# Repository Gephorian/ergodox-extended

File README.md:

# ErgoDox Extended

In a world where everyone is removing keys from their ErgoDox, I wanted more.

My goals for this keyboard were to take my existing design from 2018 and remove the Teensy,
while making it more compact, a little more stylish, and with several options for cases in
mind.

I used an ATMega32u4-au for the mcu because I wanted to be able to solder it by hand if I
needed. Same for the MCP23018-e/ss. I stuck with Mini-USB because, again, hand soldering.

There are options for SMD or through-hole diodes.

Cherry keyswitches, I've never used Gaterons or any others so I can't say whether they
would be compatible with the pcb.

This board works just like the original ErgoDox board; the same board can be used for
either half of the keyboard. Solder the logic components on the front, and diodes on the
front or back of the board. The silkscreen for diode direction is set up for `Row2Col` in
the firmware.

Everything should be included in the kicad project aside from the firmware. Make sure
to clone recursively so that it pulls the submodule(s).

Firmware is [here](https://github.com/Gephorian/qmk_firmware/tree/ergodox-extended) until
I get a PR merged into QMK.

## Manufacturing

I've used JLCPCB and Elecrow. Both are great. Go for 1.6mm, whatever color you want is
fine. I was able to generate a BOM using JLCPCB's plugin and get it partially assembled,
so that takes a lot of guesswork out of the soldering and debugging if you go that route.

## Contributing

Feel free to submit PRs and issues for fixes.

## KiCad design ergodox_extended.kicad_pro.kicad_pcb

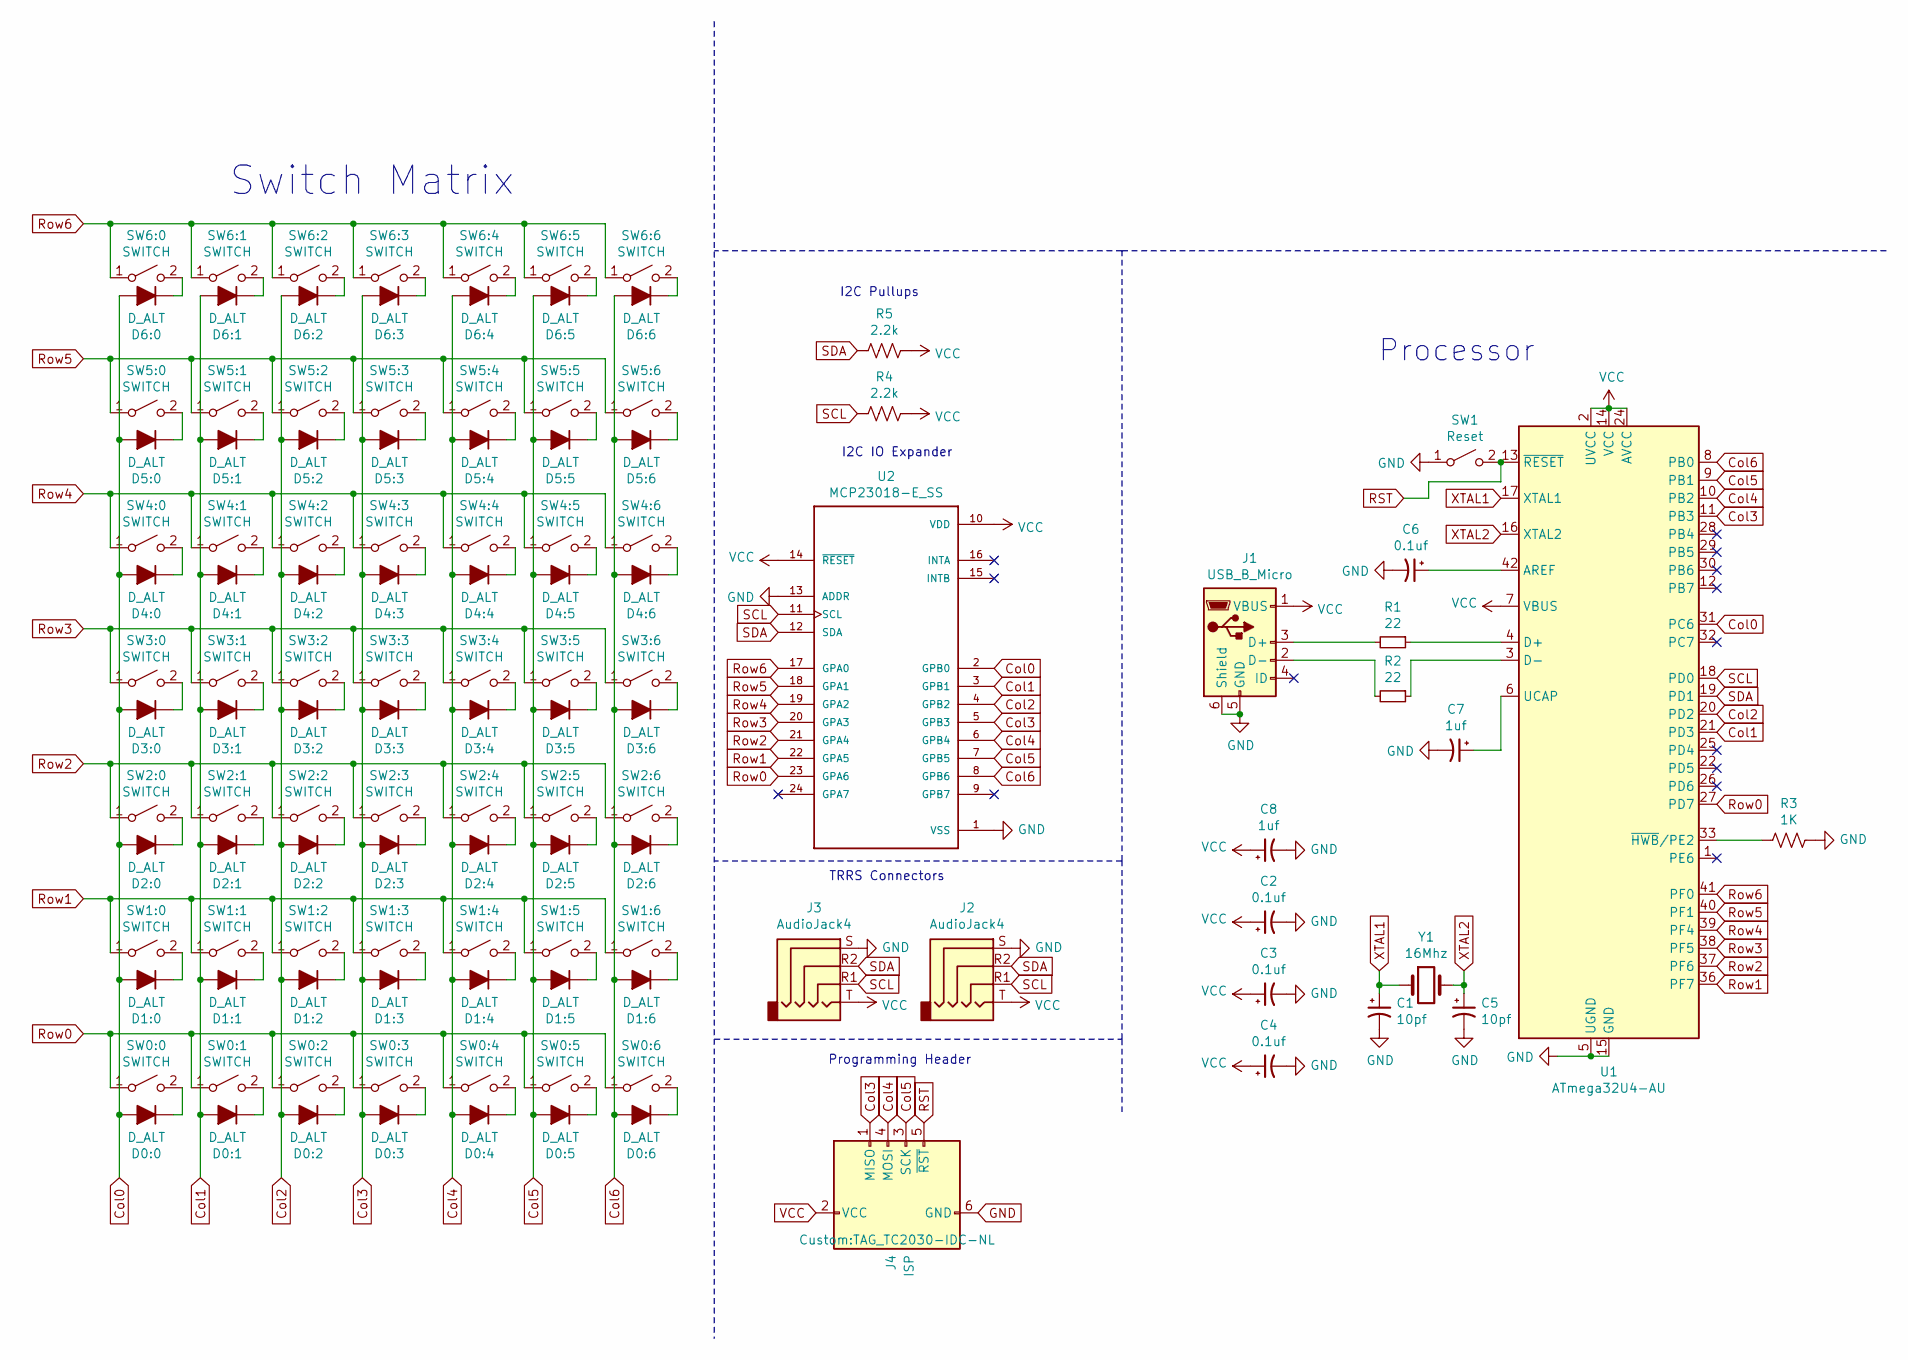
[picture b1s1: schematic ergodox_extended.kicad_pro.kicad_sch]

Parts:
C1, C5: 10pf; C_0402_1005Metric
C2, C3, C4, C6: 0.1uf; C_0603_1608Metric
C7, C8: 1uf; C_0805_2012Metric
D0:0, D0:1, D0:2, D0:3, D0:4, D0:5, D0:6, D1:0, D1:1, D1:2, D1:3, D1:4, D1:5, D1:6, D2:0, D2:1, D2:2, D2:3, D2:4, D2:5, D2:6, D3:0, D3:1, D3:2, D3:3, D3:4, D3:5, D3:6, D4:0, D4:1, D4:2, D4:3, D4:4, D4:5, D4:6, D5:0, D5:1, D5:2, D5:3, D5:4, D5:5, D5:6, D6:0, D6:1, D6:2, D6:3, D6:4, D6:5, D6:6: D_ALT; DIODE
J1: USB_B_Micro; USBMINImod
J2, J3: AudioJack4; SJ-43514-SMT
J4: ISP; TAG_TC2030-IDC-NL
R1, R2: 22; R_0805_2012Metric
R3: 1K; R_0805_2012Metric
R4, R5: 2.2k; R_0805_2012Metric
SW0:0, SW0:1, SW0:2, SW0:3, SW0:4, SW0:5, SW0:6, SW1:0, SW1:1, SW1:2, SW1:3, SW1:4, SW1:6, SW2:1, SW2:2, SW2:3, SW2:4, SW2:5, SW2:6, SW3:1, SW3:2, SW3:3, SW3:4, SW3:5, SW4:1, SW4:2, SW4:3, SW4:4, SW4:5, SW5:1, SW5:2, SW5:3, SW5:4, SW5:5, SW5:6, SW6:0, SW6:1, SW6:2, SW6:3, SW6:4, SW6:5, SW6:6: SWITCH; CHERRY_PCB_100H
SW1: Reset; SW_SPST_B3U-1100P
SW1:5: SWITCH; CHERRY_PCB_200H
SW2:0, SW3:0, SW3:6, SW4:0, SW4:6, SW5:0: SWITCH; CHERRY_PCB_150H
U1: ATmega32U4-AU; TQFP-44_10x10mm_P0.8mm
U2: MCP23018-E_SS; SOP65P780X200-24N
Y1: 16Mhz; Crystal_SMD_3225-4Pin_3.2x2.5mm

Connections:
Col0: D0:0.2 (A), D1:0.2 (A), D2:0.2 (A), D3:0.2 (A), D4:0.2 (A), D5:0.2 (A), D6:0.2 (A), U1.31 (PC6), U2.2 (GPB0)
Col1: D0:1.2 (A), D1:1.2 (A), D2:1.2 (A), D3:1.2 (A), D4:1.2 (A), D5:1.2 (A), D6:1.2 (A), U1.21 (PD3), U2.3 (GPB1)
Col2: D0:2.2 (A), D1:2.2 (A), D2:2.2 (A), D3:2.2 (A), D4:2.2 (A), D5:2.2 (A), D6:2.2 (A), U1.20 (PD2), U2.4 (GPB2)
Col3: D0:3.2 (A), D1:3.2 (A), D2:3.2 (A), D3:3.2 (A), D4:3.2 (A), D5:3.2 (A), D6:3.2 (A), J4.1 (MISO), U1.11 (PB3), U2.5 (GPB3)
Col4: D0:4.2 (A), D1:4.2 (A), D2:4.2 (A), D3:4.2 (A), D4:4.2 (A), D5:4.2 (A), D6:4.2 (A), J4.4 (MOSI), U1.10 (PB2), U2.6 (GPB4)
Col5: D0:5.2 (A), D1:5.2 (A), D2:5.2 (A), D3:5.2 (A), D4:5.2 (A), D5:5.2 (A), D6:5.2 (A), J4.3 (SCK), U1.9 (PB1), U2.7 (GPB5)
Col6: D0:6.2 (A), D1:6.2 (A), D2:6.2 (A), D3:6.2 (A), D4:6.2 (A), D5:6.2 (A), D6:6.2 (A), U1.8 (PB0), U2.8 (GPB6)
GND: C1.2, C2.2, C3.2, C4.2, C5.2, C6.2, C7.2, C8.2, J1.5 (GND), J1.6 (Shield), J2.S, J3.S, J4.6 (GND), R3.1, SW1.1 (A), U1.5 (UGND), U1.15 (GND), U1.23 (GND), U1.35 (GND), U1.43 (GND), U2.1 (VSS), U2.13 (ADDR); also elsewhere on the board
unnamed: D0:0.1 (K), SW0:0.2 (B)
unnamed: D0:1.1 (K), SW0:1.2 (B)
unnamed: D0:2.1 (K), SW0:2.2 (B)
unnamed: D0:3.1 (K), SW0:3.2 (B)
unnamed: D0:4.1 (K), SW0:4.2 (B)
unnamed: D0:5.1 (K), SW0:5.2 (B)
unnamed: D0:6.1 (K), SW0:6.2 (B)
unnamed: D1:0.1 (K), SW1:0.2 (B)
unnamed: D1:1.1 (K), SW1:1.2 (B)
unnamed: D1:2.1 (K), SW1:2.2 (B)
unnamed: D1:3.1 (K), SW1:3.2 (B)
unnamed: D1:4.1 (K), SW1:4.2 (B)
unnamed: D1:5.1 (K), SW1:5.2 (B)
unnamed: D1:6.1 (K), SW1:6.2 (B)
unnamed: D2:0.1 (K), SW2:0.2 (B)
unnamed: D2:1.1 (K), SW2:1.2 (B)
unnamed: D2:2.1 (K), SW2:2.2 (B)
unnamed: D2:3.1 (K), SW2:3.2 (B)
unnamed: D2:4.1 (K), SW2:4.2 (B)
unnamed: D2:5.1 (K), SW2:5.2 (B)
unnamed: D2:6.1 (K), SW2:6.2 (B)
unnamed: D3:0.1 (K), SW3:0.2 (B)
unnamed: D3:1.1 (K), SW3:1.2 (B)
unnamed: D3:2.1 (K), SW3:2.2 (B)
unnamed: D3:3.1 (K), SW3:3.2 (B)
unnamed: D3:4.1 (K), SW3:4.2 (B)
unnamed: D3:5.1 (K), SW3:5.2 (B)
unnamed: D3:6.1 (K), SW3:6.2 (B)
unnamed: D4:0.1 (K), SW4:0.2 (B)
unnamed: D4:1.1 (K), SW4:1.2 (B)
unnamed: D4:2.1 (K), SW4:2.2 (B)
unnamed: D4:3.1 (K), SW4:3.2 (B)
unnamed: D4:4.1 (K), SW4:4.2 (B)
unnamed: D4:5.1 (K), SW4:5.2 (B)
unnamed: D4:6.1 (K), SW4:6.2 (B)
unnamed: D5:0.1 (K), SW5:0.2 (B)
unnamed: D5:1.1 (K), SW5:1.2 (B)
unnamed: D5:2.1 (K), SW5:2.2 (B)
unnamed: D5:3.1 (K), SW5:3.2 (B)
unnamed: D5:4.1 (K), SW5:4.2 (B)
unnamed: D5:5.1 (K), SW5:5.2 (B)
unnamed: D5:6.1 (K), SW5:6.2 (B)
unnamed: D6:0.1 (K), SW6:0.2 (B)
unnamed: D6:1.1 (K), SW6:1.2 (B)
unnamed: D6:2.1 (K), SW6:2.2 (B)
unnamed: D6:3.1 (K), SW6:3.2 (B)
unnamed: D6:4.1 (K), SW6:4.2 (B)
unnamed: D6:5.1 (K), SW6:5.2 (B)
unnamed: D6:6.1 (K), SW6:6.2 (B)
unnamed: J1.3 (D+), R1.2
unnamed: J1.2 (D-), R2.2
unnamed: C6.1, U1.42 (AREF)
unnamed: R1.1, U1.4 (D+)
unnamed: R2.1, U1.3 (D-)
unnamed: C7.1, U1.6 (UCAP)
unnamed: R3.2, U1.33 (~HWB/PE2)
RST: J4.5 (~RST), SW1.2 (B), U1.13 (~RESET)
Row0: SW0:0.1 (A), SW0:1.1 (A), SW0:2.1 (A), SW0:3.1 (A), SW0:4.1 (A), SW0:5.1 (A), SW0:6.1 (A), U1.27 (PD7), U2.23 (GPA6)
Row1: SW1:0.1 (A), SW1:1.1 (A), SW1:2.1 (A), SW1:3.1 (A), SW1:4.1 (A), SW1:5.1 (A), SW1:6.1 (A), U1.36 (PF7), U2.22 (GPA5)
Row2: SW2:0.1 (A), SW2:1.1 (A), SW2:2.1 (A), SW2:3.1 (A), SW2:4.1 (A), SW2:5.1 (A), SW2:6.1 (A), U1.37 (PF6), U2.21 (GPA4)
Row3: SW3:0.1 (A), SW3:1.1 (A), SW3:2.1 (A), SW3:3.1 (A), SW3:4.1 (A), SW3:5.1 (A), SW3:6.1 (A), U1.38 (PF5), U2.20 (GPA3)
Row4: SW4:0.1 (A), SW4:1.1 (A), SW4:2.1 (A), SW4:3.1 (A), SW4:4.1 (A), SW4:5.1 (A), SW4:6.1 (A), U1.39 (PF4), U2.19 (GPA2)
Row5: SW5:0.1 (A), SW5:1.1 (A), SW5:2.1 (A), SW5:3.1 (A), SW5:4.1 (A), SW5:5.1 (A), SW5:6.1 (A), U1.40 (PF1), U2.18 (GPA1)
Row6: SW6:0.1 (A), SW6:1.1 (A), SW6:2.1 (A), SW6:3.1 (A), SW6:4.1 (A), SW6:5.1 (A), SW6:6.1 (A), U1.41 (PF0), U2.17 (GPA0)
SCL: J2.R1, J3.R1, R4.1, U1.18 (PD0), U2.11 (SCL)
SDA: J2.R2, J3.R2, R5.2, U1.19 (PD1), U2.12 (SDA)
VCC: C2.1, C3.1, C4.1, C8.1, J1.1 (VBUS), J2.T, J3.T, J4.2 (VCC), R4.2, R5.1, U1.2 (UVCC), U1.7 (VBUS), U1.14 (VCC), U1.24 (AVCC), U1.34 (VCC), U1.44 (AVCC), U2.10 (VDD), U2.14 (~RESET)
XTAL1: C1.1, U1.17 (XTAL1), Y1.1
XTAL2: C5.1, U1.16 (XTAL2), Y1.2

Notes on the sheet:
I2C Pullups
TRRS Connectors
Switch Matrix
Programming Header
I2C IO Expander
Processor

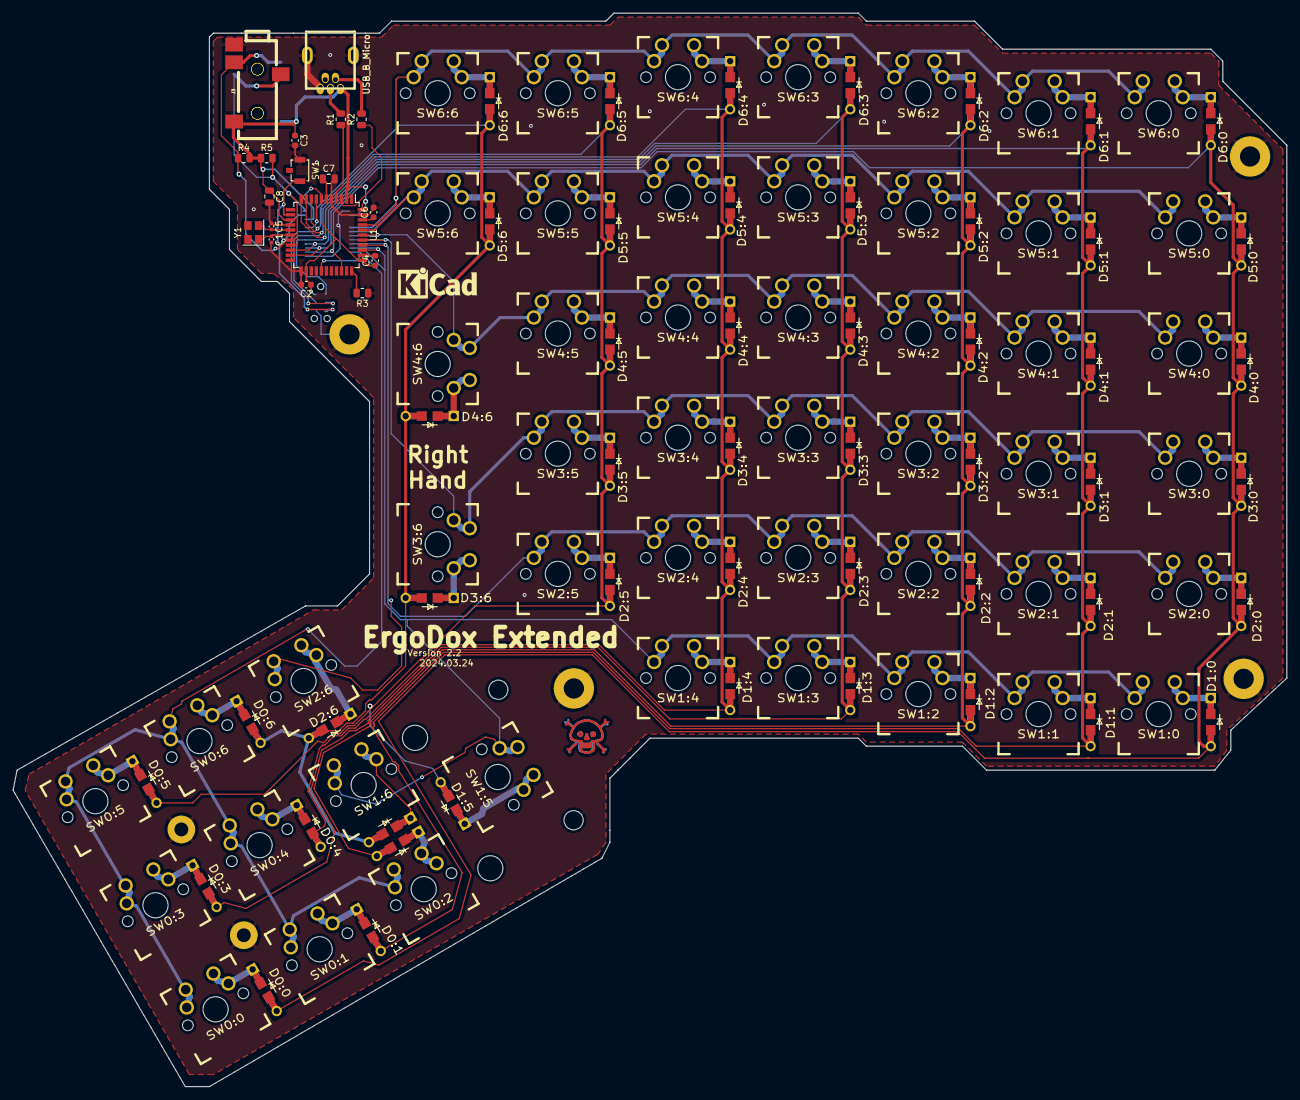
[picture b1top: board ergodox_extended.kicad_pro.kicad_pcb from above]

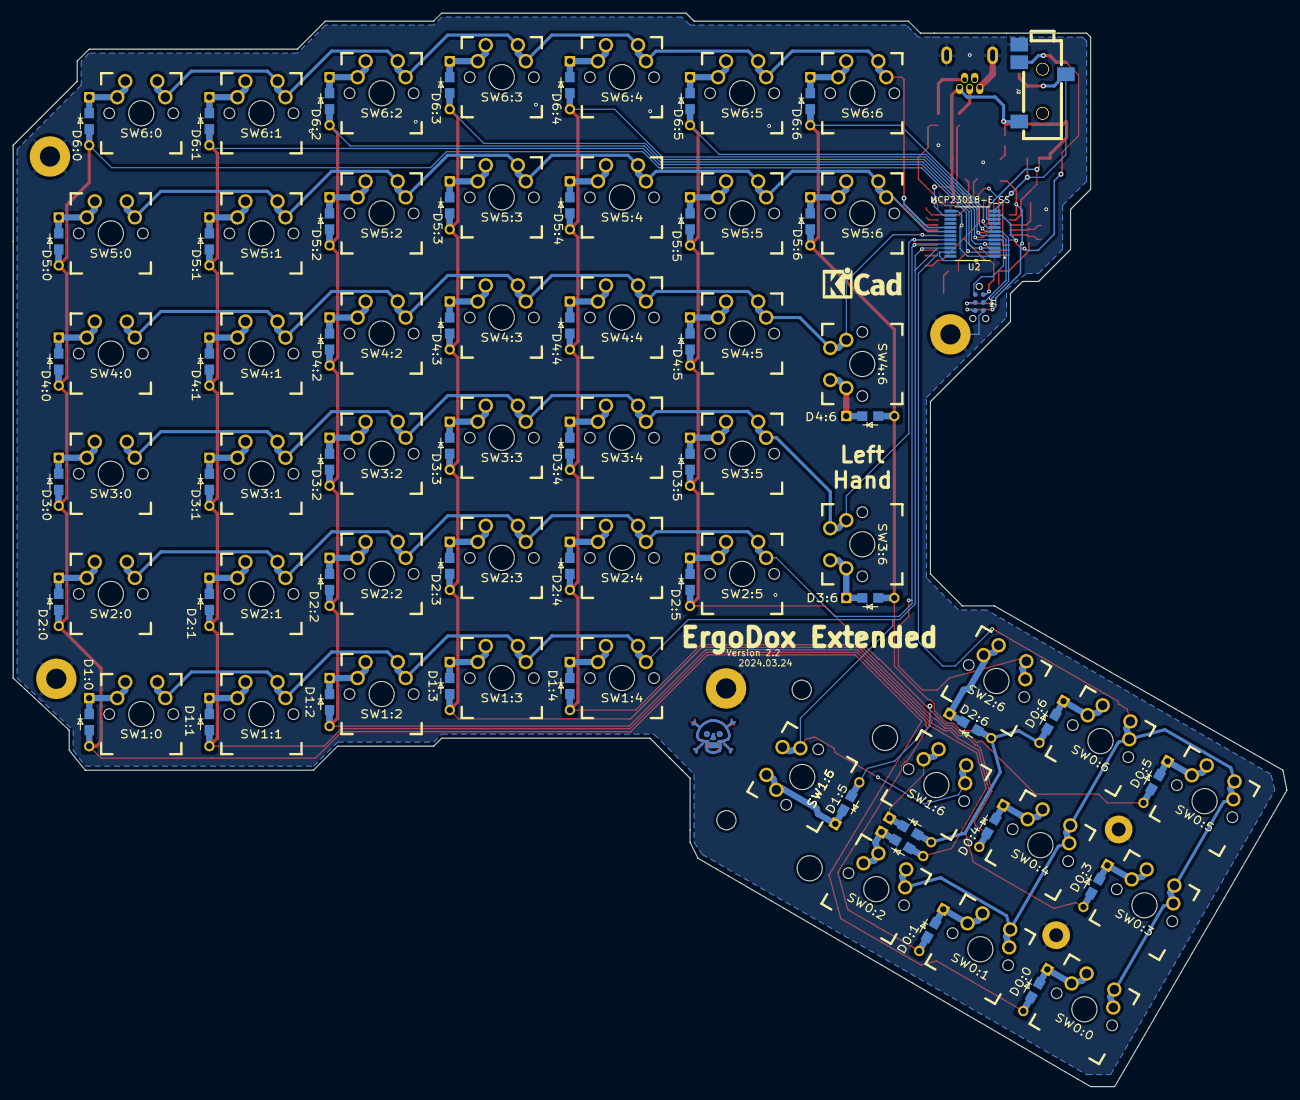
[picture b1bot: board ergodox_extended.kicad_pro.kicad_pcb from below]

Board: 2 copper layers, 201.9 x 170.2 mm, 125 parts (4 on the bottom side), 77 nets.

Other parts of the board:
MOUNT_1, MOUNT_2, MOUNT_3, MOUNT_4: MountingHole_3.2mm_M3_Pad
MOUNT_5, MOUNT_6: MountingHole_2.2mm_M2_Pad

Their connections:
GND: MOUNT_1.1, MOUNT_2.1, MOUNT_3.1, MOUNT_4.1, MOUNT_5.1, MOUNT_6.1; also elsewhere on the board

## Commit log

2024-03-24 Fix diode dir, write readme
2024-03-24 s/Micro/Mini/
